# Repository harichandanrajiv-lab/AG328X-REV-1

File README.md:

# AG328X-REV-1
AG328X REV-1 is a compact, redesigned implementation of the Arduino UNO platform, developed with
the objective of improving the original UNO architecture in terms of form factor, power architecture, USB
connectivity, protection, serviceability, and PCB integration.

The design retains the core functionality based on the ATmega328P, while keeping a dedicated
ATmega16U2 USB-to-serial interface and a redesigned power-management architecture. Rather than
directly reproducing the conventional reference design, AG328X restructures several functional sections to
achieve a more compact and integrated hardware platform.

The complete PCB is designed with an overall dimension of 34 mm × 34 mm, a 1.6 mm finished board
thickness, and a 4-layer PCB stack-up, which is 68.44% smaller in size compared to the original UNO board.
The four-layer implementation provides additional routing resources and dedicated copper areas for power
and ground distribution, enabling the compact board dimensions without compromising the electrical
organization of the design. For further info, go through @Documentation Section.

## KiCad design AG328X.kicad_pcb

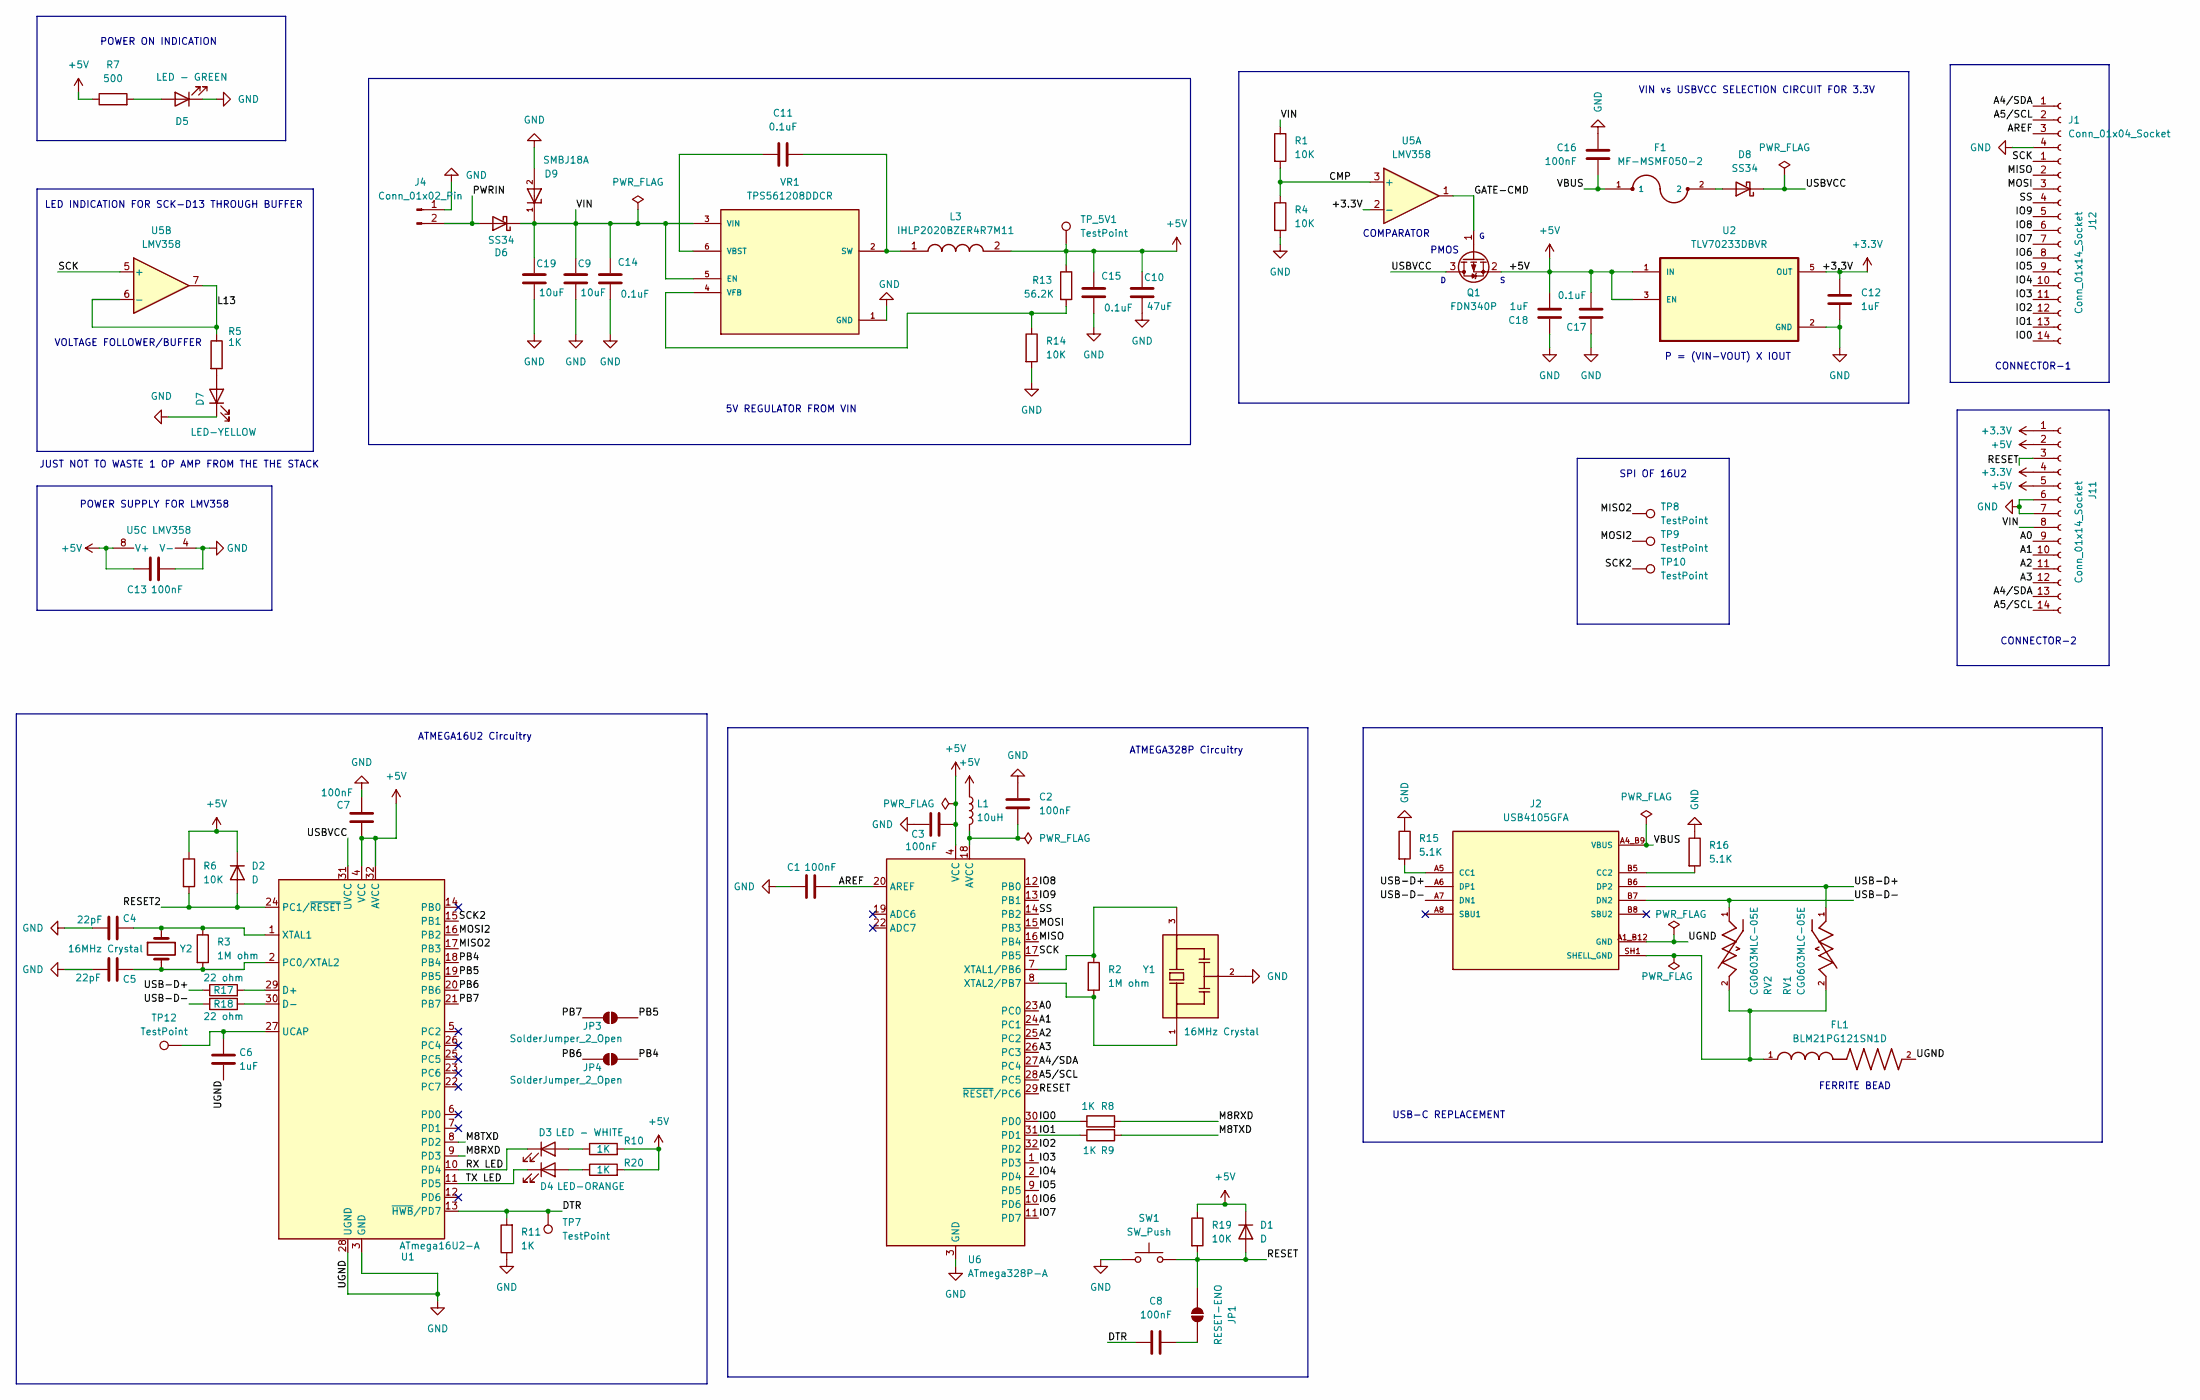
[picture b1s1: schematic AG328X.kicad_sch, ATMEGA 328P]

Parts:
C1, C2, C3, C7, C8, C13, C16: 100nF; C_0402_1005Metric
C4, C5: 22pF; C_0402_1005Metric
C6: 1uF; C_0402_1005Metric
C9, C19: 10uF; C_0603_1608Metric
C10: 47uF; C_1206_3216Metric
C11, C14, C15, C17: 0.1uF; C_0402_1005Metric
C12, C18: 1uF; C_0603_1608Metric
D1: D; D2 diode
D2: D; D_0603_1608Metric
D3: LED - WHITE; LED_0402_1005Metric
D4: LED-ORANGE; LED_0402_1005Metric
D5: LED - GREEN; LED_0402_1005Metric
D6, D8: SS34; D_SMA
D7: LED-YELLOW; LED_0402_1005Metric
D9: SMBJ18A; D_SMB_Handsoldering; PARTREV 20 - 2
F1: MF-MSMF050-2; FUSM4632X85
FL1: BLM21PG121SN1D; BEADC2012X105N
J1: Conn_01x04_Socket; PinHeader_1x04_P2.00mm_Vertical
J2: USB4105GFA; GCT_USB4105GFA; PARTREV B3
J4: Conn_01x02_Pin; JST_XA_B02B-XASK-1-A_1x02_P2.50mm_Vertical
J11, J12: Conn_01x14_Socket; PinHeader_1x14_P2.00mm_Vertical
JP1: RESET-ENO; SolderJumper-2_P1.3mm_Open_RoundedPad1.0x1.5mm
JP3, JP4: SolderJumper_2_Open; SolderJumper-2_P1.3mm_Open_RoundedPad1.0x1.5mm
L1: 10uH; L_0603_1608Metric
L3: IHLP2020BZER4R7M11; INDPM5552X200N; Manufacturer_Part_Number IHLP2020BZER4R7M11; Mouser Part Number 70-IHLP2020BZER4R7M1
Q1: FDN340P; SOT-23
R1, R4, R6, R14, R19: 10K; R_0402_1005Metric
R2, R3: 1M ohm; R_0402_1005Metric
R5, R8, R9, R10, R11, R20: 1K; R_0402_1005Metric
R7: 500; R_0402_1005Metric
R13: 56.2K; R_0402_1005Metric
R15, R16: 5.1K; R_0402_1005Metric
R17, R18: 22 ohm; R_0402_1005Metric
RV1, RV2: CG0603MLC-05E; VARC1608X56N; PARTREV E
SW1: SW_Push; SW_Tactile_SPST_NO_Straight_CK_PTS636Sx25SMTRLFS
TP7, TP8, TP9, TP10, TP12: TestPoint; TestPoint_Pad_D1.0mm
TP_5V1: TestPoint; TestPoint_Pad_D1.0mm
U1: ATmega16U2-A; TQFP-32_7x7mm_P0.8mm
U2: TLV70233DBVR; SOT95P280X145-5N
U5: LMV358; SO08
U6: ATmega328P-A; TQFP-32_7x7mm_P0.8mm
VR1: TPS561208DDCR; SOT95P280X110-6N; PARTREV April 2017
Y1: 16MHz Crystal; OSC_CSTCE16M0V53-R0; PARTREV 10/24/2022
Y2: 16MHz Crystal; 16MHz Y2

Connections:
+3.3V: C12.1, J11.1, J11.4, U2.5 (OUT), U5.2 (-)
+5V: C3.1, C7.1, C10.1, C13.2, C15.1, C17.2, C18.2, D1.1 (K), D2.1 (K), J11.2, J11.5, L1.1, L3.2, Q1.2 (S), R6.1, R7.1, R10.2, R13.1, R19.1, R20.2, TP_5V1.1 (1_1), U1.4 (VCC), U1.32 (AVCC), U2.1 (IN), U2.3 (EN), U5.8 (V+), U6.4 (VCC), U6.6 (VCC)
/A0: J11.9, U6.23 (PC0)
/A1: J11.10, U6.24 (PC1)
/A2: J11.11, U6.25 (PC2)
/A3: J11.12, U6.26 (PC3)
/A4/SDA: J1.1, J11.13, U6.27 (PC4)
/A5/SCL: J1.2, J11.14, U6.28 (PC5)
/AREF: C1.1, J1.3, U6.20 (AREF)
/CMP: R1.2, R4.1, U5.3 (+)
/DTR: C8.1, R11.2, TP7.1 (1_1), U1.13 (~HWB/PD7)
/GATE-CMD: Q1.1 (G), U5.1
/IO0: J12.14, R8.1, U6.30 (PD0)
/IO1: J12.13, R9.1, U6.31 (PD1)
/IO2: J12.12, U6.32 (PD2)
/IO3: J12.11, U6.1 (PD3)
/IO4: J12.10, U6.2 (PD4)
/IO5: J12.9, U6.9 (PD5)
/IO6: J12.8, U6.10 (PD6)
/IO7: J12.7, U6.11 (PD7)
/IO8: J12.6, U6.12 (PB0)
/IO9: J12.5, U6.13 (PB1)
/L13: R5.1, U5.6 (-), U5.7
/M8RXD: R8.2, U1.9 (PD3)
/M8TXD: R9.2, U1.8 (PD2)
/MISO: J12.2, U6.16 (PB4)
/MISO2: TP8.1 (1_1), U1.17 (PB3)
/MOSI: J12.3, U6.15 (PB3)
/MOSI2: TP9.1 (1_1), U1.16 (PB2)
/PB4: JP4.2 (B), U1.18 (PB4)
/PB5: JP3.2 (B), U1.19 (PB5)
/PB6: JP4.1 (A), U1.20 (PB6)
/PB7: JP3.1 (A), U1.21 (PB7)
/PWRIN: D6.2 (A), J4.2
/RESET: D1.2 (A), J11.3, JP1.2 (B), R19.2, SW1.2, U6.29 (~RESET/PC6)
/RESET2: D2.2 (A), R6.2, U1.24 (PC1/~RESET)
/RX LED: D3.1 (K), U1.10 (PD4)
/SCK: J12.1, U5.5 (+), U6.17 (PB5)
/SCK2: TP10.1 (1_1), U1.15 (PB1)
/SS: J12.4, U6.14 (PB2)
/TX LED: D4.1 (K), U1.11 (PD5)
/USB-D+: J2.A6 (DP1), J2.B6 (DP2), R17.1, RV1.1
/USB-D-: J2.A7 (DN1), J2.B7 (DN2), R18.2, RV2.1
/USBVCC: D8.1 (K), Q1.3 (D), U1.31 (UVCC)
/VIN: C9.1, C14.1, C19.1, D6.1 (K), D9.1, J11.8, R1.1, VR1.3 (VIN), VR1.5 (EN)
GND: C1.2, C2.2, C3.2, C4.1, C5.1, C6.2, C7.2, C9.2, C10.2, C12.2, C13.1, C14.2, C15.2, C16.2, C17.1, C18.1, C19.2, D5.1 (K), D7.1 (K), D9.2, FL1.2, J1.4, J2.A1_B12 (GND), J2.B1_A12 (GND), J4.1, J11.6, J11.7, R4.2, R11.1, R14.2, R15.1, R16.1, SW1.1, U1.3 (GND), U1.28 (UGND), U2.2 (GND), U5.4 (V-), U6.3 (GND), U6.5 (GND), U6.21 (GND), VR1.1 (GND), Y1.2
unnamed: D3.2 (A), R10.1
unnamed: D4.2 (A), R20.1
unnamed: D5.2 (A), R7.2
unnamed: D7.2 (A), R5.2
unnamed: D8.2 (A), F1.2
unnamed: J2.A5 (CC1), R15.2
unnamed: J2.B5 (CC2), R16.2
unnamed: C8.2, JP1.1 (A)
unnamed: R17.2, U1.29 (D+)
unnamed: R18.1, U1.30 (D-)
unnamed: C5.2, R3.2, U1.2 (PC0/XTAL2), Y2.2
unnamed: C6.1, TP12.1 (1_1), U1.27 (UCAP)
unnamed: C4.2, R3.1, U1.1 (XTAL1), Y2.1
unnamed: C2.1, L1.2, U6.18 (AVCC)
unnamed: R2.1, U6.7 (XTAL1/PB6), Y1.3
unnamed: R2.2, U6.8 (XTAL2/PB7), Y1.1
unnamed: C11.1, L3.1, VR1.2 (SW)
unnamed: C11.2, VR1.6 (VBST)
unnamed: R13.2, R14.1, VR1.4 (VFB)
SHELL_GND: FL1.1, J2.SH1 (SHELL_GND), J2.SH2 (SHELL_GND), J2.SH3 (SHELL_GND), J2.SH4 (SHELL_GND), RV1.2, RV2.2
VBUS: C16.1, F1.1, J2.A4_B9 (VBUS), J2.B4_A9 (VBUS)

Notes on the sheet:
LED INDICATION FOR SCK-D13 THROUGH BUFFER
ATMEGA328P Circuitry
POWER ON INDICATION
SPI OF 16U2
5V REGULATOR FROM VIN
P = (VIN-VOUT) X IOUT
VOLTAGE FOLLOWER/BUFFER
COMPARATOR
ATMEGA16U2 Circuitry
JUST NOT TO WASTE 1 OP AMP FROM THE THE STACK
POWER SUPPLY FOR LMV358
PMOS
CONNECTOR-1
USB-C REPLACEMENT
CONNECTOR-2
FERRITE BEAD
VIN vs USBVCC SELECTION CIRCUIT FOR 3.3V

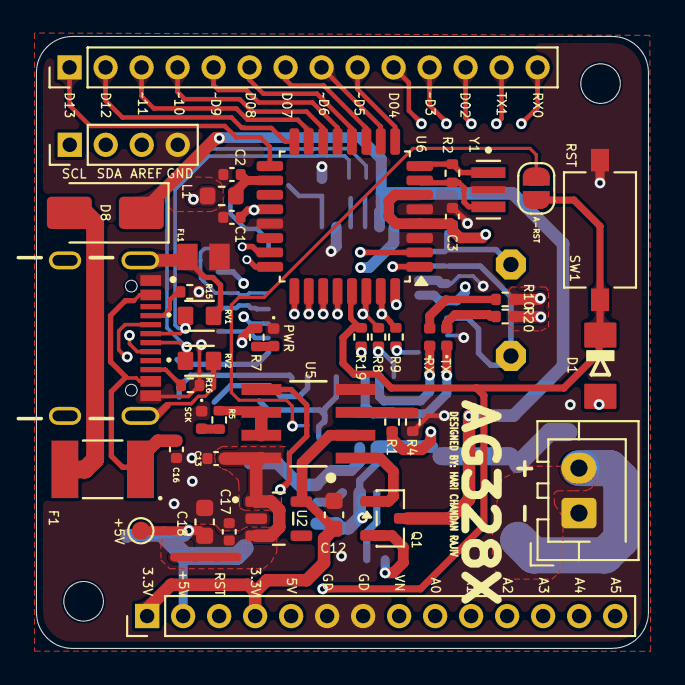
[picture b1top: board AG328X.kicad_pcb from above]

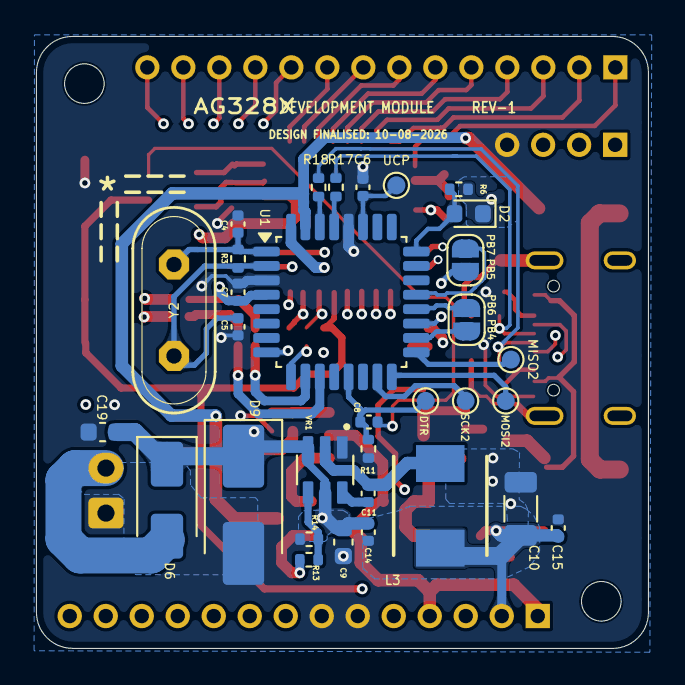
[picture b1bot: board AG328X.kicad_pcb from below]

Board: 4 copper layers, 34.0 x 34.0 mm, 76 parts (32 on the bottom side), 67 nets.

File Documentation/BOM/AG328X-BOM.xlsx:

AG328X
Id | Designator | Footprint | Designation | Quantity | Cost | Total | Source Link
1 | C1, C2, C3, C7, C8, C13, C16 | C_0402_1005Metric | 100nF | 7 | 0.5 | 3.5 | https://robu.in/product/gcm155r71h104ke02j-murata-electronic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
2 | C4, C5 | C_0402_1005Metric | 22pF | 2 | 0.23 | 0.46 | https://robu.in/product/grm1555c1h220ga01d-murata-cap-cerami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
3 | C6 | C_0402_1005Metric | 1uF | 1 | 0.31 | 0.31 | https://robu.in/product/grm155b31c105ka12d-murata-cap-cerami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
4 | C9, C19 | C_0603_1608Metric | 10uF | 2 | 2.34 | 4.68 | https://robu.in/product/grm188r61e106ma73d-murata-cap-cerami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
5 | C10 | C_1206_3216Metric | 47uF | 1 | 33 | 33 | https://robu.in/product/grm31cr61e476me44l-murata-25v-47uf-x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
6 | C11, C14, C15, C17 | C_0402_1005Metric | 0.1uF | 4 | 0.5 | 2 | https://robu.in/product/gcm155r71h104ke02j-murata-electronic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
7 | C12, C18 | C_0603_1608Metric | 1uF | 2 | 0.5 | 1 | https://robu.in/product/grm188r71e105ka12d-murata-cap-cerami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
8 | D1 | SS14 | DO-214AC | 1 | 1.35 | 1.35 | https://robu.in/product/ss14-slkor-40v-550mv1a-1a-smado-214a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
9 | D2 | D_0603_1608Metric | SDM2U30CSP-7B | 1 | 16 | 16 | https://robu.in/product/sdm2u30csp-7b-diodes-incorporated-30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
10 | D3 | LED_0402_1005Metric | LED - WHITE | 1 | 1.69 | 1.69 | https://robu.in/product/0402-surface-mount-led-white/
11 | D4 | LED_0402_1005Metric | LED-ORANGE | 1 | 1.79 | 1.79 | https://robu.in/product/0402-surface-mount-led-orange/
12 | D5 | LED_0402_1005Metric | LED - GREEN | 1 | 1.91 | 1.91 | https://robu.in/product/0402-surface-mount-led-green-50-pcs/
13 | D6, D8 | D_SMA | SS34 | 2 | 2.47 | 4.94 | https://robu.in/product/ss34-slkor-40v-500mv3a-3a-smado-214a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
14 | D7 | LED_0402_1005Metric | LED-YELLOW | 1 | 1.77 | 1.77 | https://robu.in/product/0402-surface-mount-led-yellow/
15 | D9 | D_SMB_Handsoldering | SMBJ18A | 1 | 20 | 20 | https://robu.in/product/smbj18a-13-f-diodes-incorporated-20-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
16 | F1 | FUSM4632X85 | MF-MSMF050-2 | 1 | 40.77 | 40.77 | https://www.lioncircuits.com/parts/MF-MSMF050-2?srsltid=AfmB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
17 | FL1 | BEADC2012X105N | BLM21PG121SN1D | 1 | 15.93 | 15.93 | https://www.lioncircuits.com/parts/BLM21PG121SN1D?srsltid=Af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
18 | J1 | PinHeader_1x04_P2.00mm_Vertical | Conn_01x04_Socket | 1 | 0 | 0 | https://robu.in/product/2mm-pitch-male-berg-strip-40x1-2pcs/
19 | J2 | GCT_USB4105GFA | USB4105GFA | 1 | 5.5 | 5.5 | https://www.ktron.in/product/16-pin-usb-type-c-connector-smd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
20 | J4 | JST_XA_B02B-XASK-1-A_1x02_P2.50mm_Vertical | Conn_01x02_Pin | 1 | 8 | 8 | https://robu.in/product/2-pin-jst-xh-2-54mm-pitch-plug-and-s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
21 | J11, J12 | PinHeader_1x14_P2.00mm_Vertical | Conn_01x14_Socket | 2 | 12.5 | 25 | https://robu.in/product/2mm-pitch-male-berg-strip-40x1-2pcs/
22 | L1 | L_0603_1608Metric | 10uH | 1 | 3.73 | 3.73 | https://robu.in/product/mlz1608m100wt000-tdk-10-%C2%B5h-shie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
23 | L3 | INDPM5552X200N | IHLP2020BZER4R7M11 | 1 | 12 | 12 | https://robu.in/product/ihlp2020bzer4r7m11-vishay-power-indu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
24 | Q1 | SOT-23 | FDN340P | 1 | 6 | 6 | https://robu.in/product/fdn340p-slkor-20v-3a-1w-70m%CF%894-5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
25 | R1, R4, R6, R14, R19 | R_0402_1005Metric | 10K | 5 | 0.36 | 1.8 | https://robu.in/product/rc0402fr-1010kl-yageo-0-063w-thick-f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
26 | R2, R3 | R_0402_1005Metric | 1M ohm | 2 | 0.67 | 1.34 | https://robu.in/product/rc0402fr-071ml-yageo-res-thick-film-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
27 | R5, R8, R9, R10, R11, R20 | R_0402_1005Metric | 1K | 6 | 0.68 | 4.08 | https://robu.in/product/ac0402jr-071kl-yageo-res-thick-film-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
28 | R7 | R_0402_1005Metric | 500 | 1 | 0 | 0 | Use 1k
29 | R13 | R_0402_1005Metric | 56.2K | 1 | 0.12 | 0.12 | https://robu.in/product/ac0402fr-0756k2l-yageo-res-thick-fil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
30 | R15, R16 | R_0402_1005Metric | 5.1K | 2 | 0.13 | 0.26 | https://robu.in/product/rc0402fr-075k1l-yageo-smd-chip-resistor/
31 | R17, R18 | R_0402_1005Metric | 22 ohm | 2 | 0.6899999999999999 | 1.38 | https://robu.in/product/rc0402fr-0722rl-yageo-smd-chip-resis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
32 | RV1, RV2 | VARC1608X56N | CG0603MLC-05E | 2 | 27 | 54 | https://robu.in/product/cg0603mlc-05e-bourns-tvs-varistor-8-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
33 | SW1 | SW_Tactile_SPST_NO_Straight_CK_PTS636Sx25SMTRLFS | SW_Push | 1 | 2.71 | 2.71 | https://robu.in/product/lck-ta007h27-2wl-lckelec-362-7-patch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
35 | U1 | TQFP-32_7x7mm_P0.8mm | ATmega16U2-A | 1 | 364.679 | 364.679 | https://in.element14.com/microchip/atmega16u2-au/mcu-8bit-16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
36 | U2 | SOT95P280X145-5N | TLV70233DBVR | 1 | 15.05 | 15.05 | https://www.ktron.in/product/tlv70233dbvr-regulator-ic/
37 | U5 | SO08 | LMV358 | 1 | 11 | 11 | https://robu.in/product/lmv358-slkor-dual-0-3v-us-1mhz-9mv-s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
38 | U6 | TQFP-32_7x7mm_P0.8mm | ATmega328P-A | 1 | 326 | 326 | https://robu.in/product/atmega328p-au-microchip-8-bit-mcu-av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
39 | VR1 | SOT95P280X110-6N | TPS561208DDCR | 1 | 54 | 54 | https://robu.in/product/tps561208ddcr-texas-instruments-step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
40 | Y1 | OSC_CSTCE16M0V53-R0 | 16MHz Crystal | 1 | 37.52 | 37.52 | https://www.lioncircuits.com/parts/CSTNE16M0VH3C000R0?srslti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
41 | Y2 | 16MHz Y2 | 16MHz Crystal | 1 | 8 | 8 | https://robu.in/product/hc49-s-16mhz-crystal-oscillator-pack-of-5/
 |  |  |  |  |  | 1093.269
